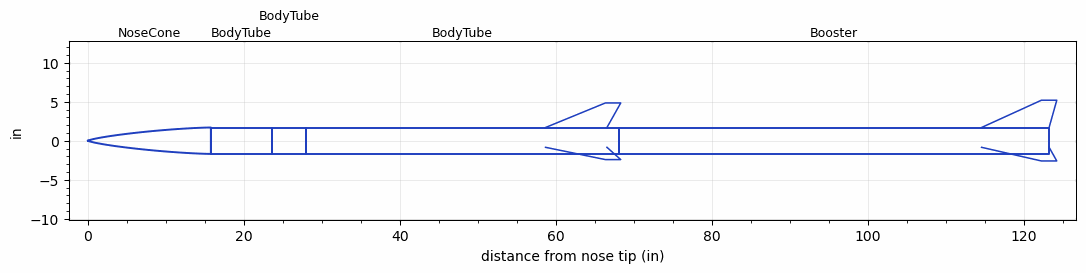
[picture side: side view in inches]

<RASAeroDocument>
 <FileVersion>2</FileVersion>
 <RocketDesign>
  <NoseCone>
   <Length>15.748</Length>
   <Diameter>3.3858</Diameter>
   <Shape>Von Karman Ogive</Shape>
   <Location>0</Location>
  </NoseCone>
  <BodyTube>
   <Length>7.874</Length>
   <Diameter>3.3858</Diameter>
   <Location>15.748</Location>
  </BodyTube>
  <BodyTube>
   <Length>4.3307</Length>
   <Diameter>3.3858</Diameter>
   <Location>23.622</Location>
  </BodyTube>
  <BodyTube>
   <Length>40.1574</Length>
   <Diameter>3.3858</Diameter>
   <Location>27.9527</Location>
   <Fin>
    <Count>3</Count>
    <Chord>7.874</Chord>
    <Span>3.1496</Span>
    <SweepDistance>7.6772</SweepDistance>
    <TipChord>1.9685</TipChord>
    <Thickness>0.125</Thickness>
    <Location>9.4488</Location>
    <AirfoilSection>Rounded</AirfoilSection>
   </Fin>
  </BodyTube>
  <Booster>
   <Length>55.118</Length>
   <Diameter>3.3858</Diameter>
   <Location>68.1101</Location>
   <Fin>
    <Count>3</Count>
    <Chord>8.6614</Chord>
    <Span>3.5</Span>
    <SweepDistance>7.6772</SweepDistance>
    <TipChord>1.9685</TipChord>
    <Thickness>0.125</Thickness>
    <Location>8.6614</Location>
    <AirfoilSection>Rounded</AirfoilSection>
   </Fin>
  </Booster>
  <Surface>Sheet Metal</Surface>
  <CD>0</CD>
  <ModifiedBarrowman>False</ModifiedBarrowman>
  <Turbulence>False</Turbulence>
  <UseBooster1>True</UseBooster1>
  <UseBooster2>False</UseBooster2>
 </RocketDesign>
 <LaunchSite>
  <Altitude>1249</Altitude>
  <Pressure>28.6029</Pressure>
  <RodAngle>0</RodAngle>
  <RodLength>39.37</RodLength>
  <Temperature>54.5459</Temperature>
  <WindSpeed>4.4739</WindSpeed>
 </LaunchSite>
 <Recovery>
  <Altitude1>656.168</Altitude1>
  <Altitude2>656.168</Altitude2>
  <DeviceType1>Parachute</DeviceType1>
  <DeviceType2>Parachute</DeviceType2>
  <Event1>True</Event1>
  <Event2>True</Event2>
  <Size1>39.9999</Size1>
  <Size2>15</Size2>
  <EventType1>Altitude</EventType1>
  <EventType2>Apogee</EventType2>
  <CD1>0.8</CD1>
  <CD2>0</CD2>
 </Recovery>
 <SimulationList>
  <Simulation>
   <SustainerEngine>M1315W  (AT)</SustainerEngine>
   <SustainerLaunchWt>18.1407</SustainerLaunchWt>
   <SustainerCG>46.3655</SustainerCG>
   <SustainerIgnitionDelay>20</SustainerIgnitionDelay>
   <Booster1Engine>M1315W  (AT)</Booster1Engine>
   <Booster1LaunchWt>35.6997</Booster1LaunchWt>
   <Booster1SeparationDelay>1</Booster1SeparationDelay>
   <Booster1IgnitionDelay>0</Booster1IgnitionDelay>
   <Booster1CG>74.0256</Booster1CG>
   <IncludeBooster1>True</IncludeBooster1>
   <Booster2Delay>0</Booster2Delay>
   <IncludeBooster2>False</IncludeBooster2>
  </Simulation>
  <Simulation>
   <SustainerLaunchWt>13.9674</SustainerLaunchWt>
   <SustainerCG>48.2517</SustainerCG>
   <SustainerIgnitionDelay>16</SustainerIgnitionDelay>
   <Booster1LaunchWt>27.353</Booster1LaunchWt>
   <Booster1SeparationDelay>1</Booster1SeparationDelay>
   <Booster1IgnitionDelay>0</Booster1IgnitionDelay>
   <Booster1CG>75.9827</Booster1CG>
   <IncludeBooster1>True</IncludeBooster1>
   <Booster2Delay>0</Booster2Delay>
   <IncludeBooster2>False</IncludeBooster2>
  </Simulation>
  <Simulation>
   <SustainerEngine>K780R  (AT)</SustainerEngine>
   <SustainerLaunchWt>12.1653</SustainerLaunchWt>
   <SustainerCG>46.5702</SustainerCG>
   <SustainerIgnitionDelay>4</SustainerIgnitionDelay>
   <Booster1Engine>K780R  (AT)</Booster1Engine>
   <Booster1LaunchWt>23.7489</Booster1LaunchWt>
   <Booster1SeparationDelay>1</Booster1SeparationDelay>
   <Booster1IgnitionDelay>0</Booster1IgnitionDelay>
   <Booster1CG>74.2861</Booster1CG>
   <IncludeBooster1>True</IncludeBooster1>
   <Booster2Delay>0</Booster2Delay>
   <IncludeBooster2>False</IncludeBooster2>
  </Simulation>
  <Simulation>
   <SustainerEngine>M650W  (AT)</SustainerEngine>
   <SustainerLaunchWt>16.9948</SustainerLaunchWt>
   <SustainerCG>45.9625</SustainerCG>
   <SustainerIgnitionDelay>8</SustainerIgnitionDelay>
   <Booster1LaunchWt>30.208</Booster1LaunchWt>
   <Booster1SeparationDelay>1</Booster1SeparationDelay>
   <Booster1IgnitionDelay>0</Booster1IgnitionDelay>
   <Booster1CG>71.4737</Booster1CG>
   <IncludeBooster1>True</IncludeBooster1>
   <Booster2Delay>0</Booster2Delay>
   <IncludeBooster2>False</IncludeBooster2>
  </Simulation>
  <Simulation>
   <SustainerEngine>L2200G  (AT)</SustainerEngine>
   <SustainerLaunchWt>16.1702</SustainerLaunchWt>
   <SustainerCG>46.9633</SustainerCG>
   <SustainerIgnitionDelay>6</SustainerIgnitionDelay>
   <Booster1Engine>L2200G  (AT)</Booster1Engine>
   <Booster1LaunchWt>31.7587</Booster1LaunchWt>
   <Booster1SeparationDelay>1</Booster1SeparationDelay>
   <Booster1IgnitionDelay>0</Booster1IgnitionDelay>
   <Booster1CG>74.6468</Booster1CG>
   <IncludeBooster1>True</IncludeBooster1>
   <Booster2Delay>0</Booster2Delay>
   <IncludeBooster2>False</IncludeBooster2>
  </Simulation>
  <Simulation>
   <SustainerEngine>K560W  (AT)</SustainerEngine>
   <SustainerLaunchWt>11.6784</SustainerLaunchWt>
   <SustainerCG>47.1421</SustainerCG>
   <SustainerIgnitionDelay>19</SustainerIgnitionDelay>
   <Booster1Engine>L2200G  (AT)</Booster1Engine>
   <Booster1LaunchWt>27.2669</Booster1LaunchWt>
   <Booster1SeparationDelay>1</Booster1SeparationDelay>
   <Booster1IgnitionDelay>0</Booster1IgnitionDelay>
   <Booster1CG>79.2838</Booster1CG>
   <IncludeBooster1>True</IncludeBooster1>
   <Booster2Delay>0</Booster2Delay>
   <IncludeBooster2>False</IncludeBooster2>
  </Simulation>
 </SimulationList>
</RASAeroDocument>
